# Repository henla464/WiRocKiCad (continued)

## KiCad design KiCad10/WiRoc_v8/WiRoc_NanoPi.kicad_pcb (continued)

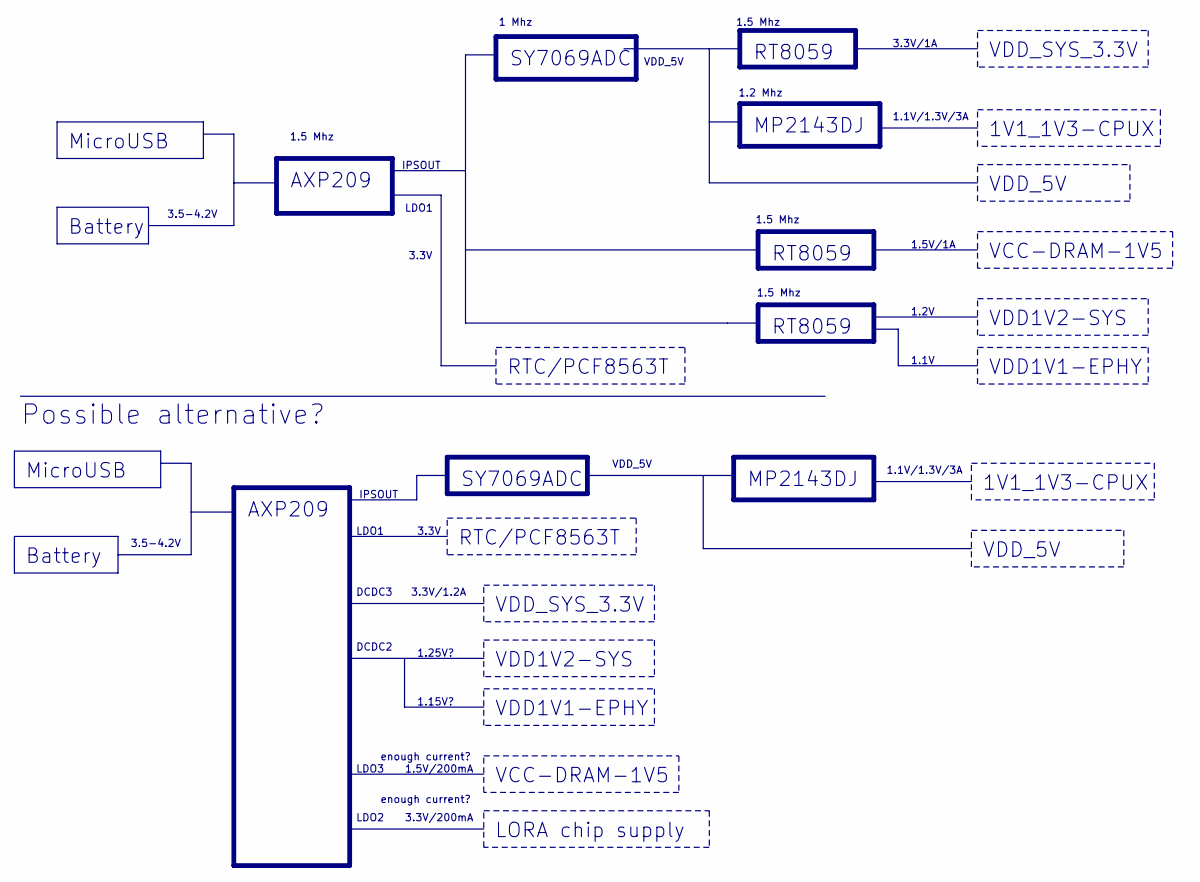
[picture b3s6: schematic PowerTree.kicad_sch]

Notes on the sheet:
1.5 Mhz
1.5V/1A
3.5-4.2V
DCDC3
1.1V/1.3V/3A
Possible alternative?
3.3V/1.2A
1.5V/200mA
1.25V?
IPSOUT
1 Mhz
LDO2
3.3V/1A
3.3V/200mA
1.2V
1.15V?
DCDC2
VDD_5V
LDO1
1.2 Mhz
LDO3
3.3V
1.1V
enough current?
VDD1V1-EPHY
1V1_1V3-CPUX
MicroUSB
RTC/PCF8563T
SY7069ADC
Battery
VDD1V2-SYS
MP2143DJ
RT8059
VDD_SYS_3.3V
AXP209
VCC-DRAM-1V5
LORA chip supply

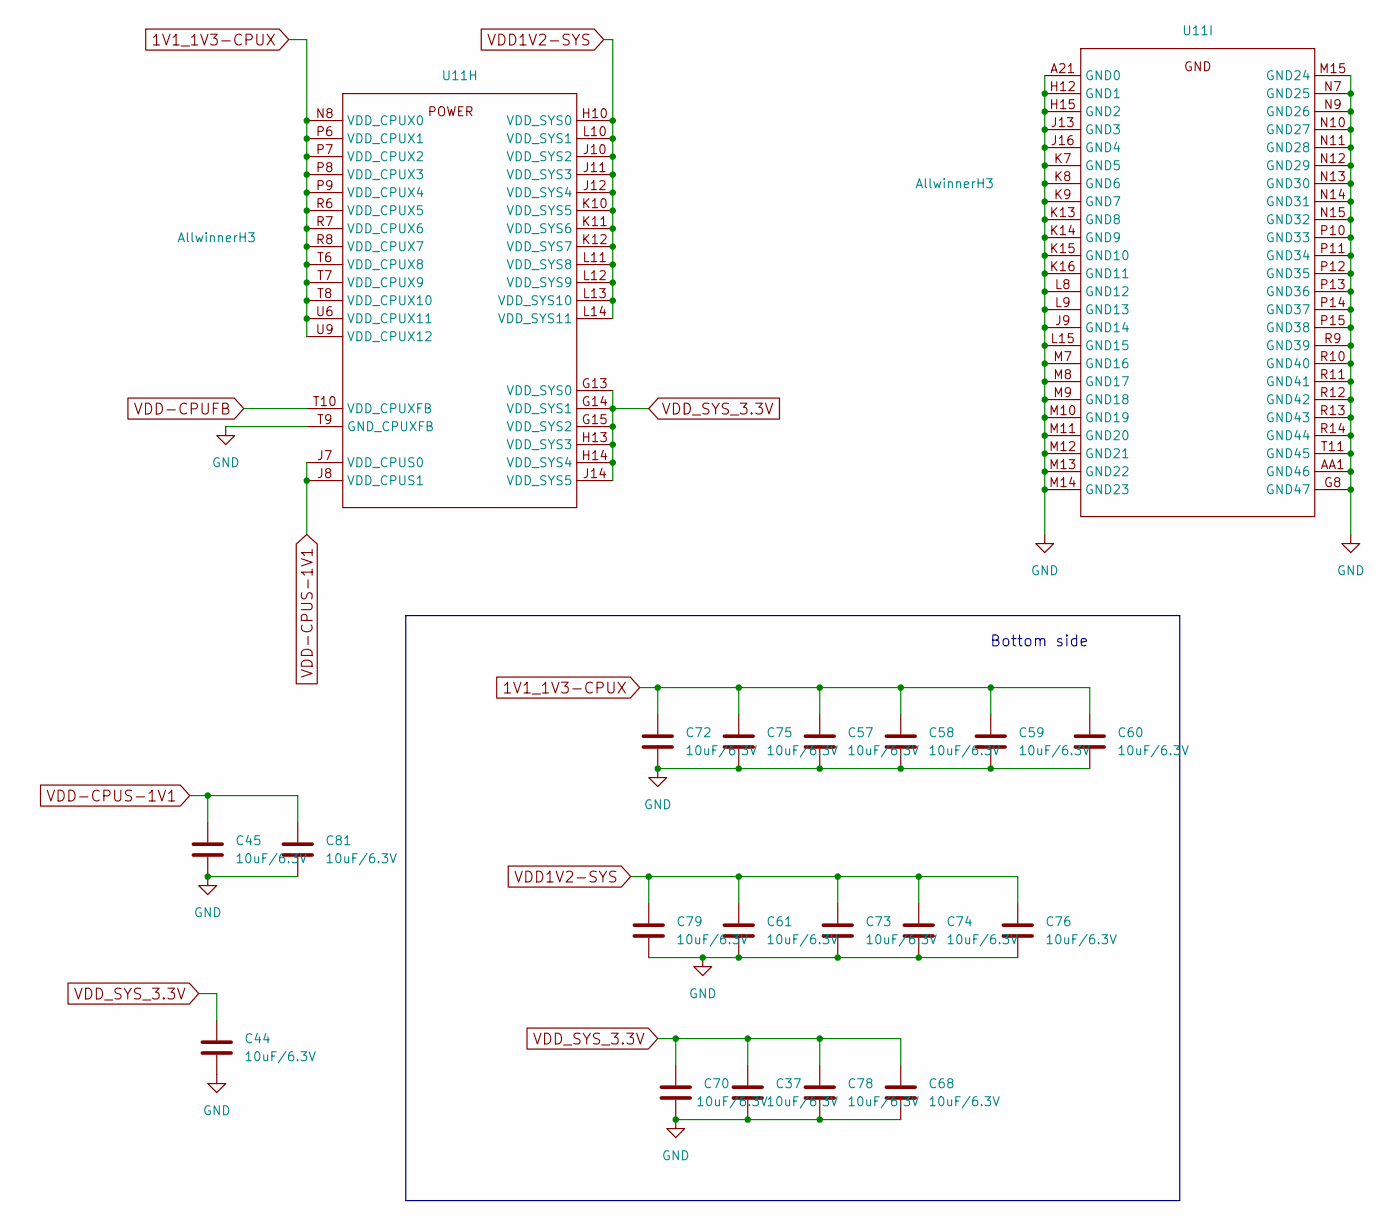
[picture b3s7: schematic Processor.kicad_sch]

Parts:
C37, C44, C45, C57, C58, C59, C60, C61, C68, C70, C72, C73, C74, C75, C76, C78, C79, C81: 10uF/6.3V; C_0402_1005Metric; ManufacturerPartNumber CL05A106MQ5NUNC; LCSC Part # C15525
U11: AllwinnerH3; BGA-347_21x21_14.0x14.0mm; ManufacturerPartNumber H3; JLCBasicExtended Extended

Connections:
1V1_1V3-CPUX: C57.1, C58.1, C59.1, C60.1, C72.1, C75.1, U11.N8 (VDD_CPUX0), U11.P6 (VDD_CPUX1), U11.P7 (VDD_CPUX2), U11.P8 (VDD_CPUX3), U11.P9 (VDD_CPUX4), U11.R6 (VDD_CPUX5), U11.R7 (VDD_CPUX6), U11.R8 (VDD_CPUX7), U11.T6 (VDD_CPUX8), U11.T7 (VDD_CPUX9), U11.T8 (VDD_CPUX10), U11.U6 (VDD_CPUX11), U11.U9 (VDD_CPUX12); also elsewhere on the board
GND: C37.2, C44.2, C45.2, C57.2, C58.2, C59.2, C60.2, C61.2, C68.2, C70.2, C72.2, C73.2, C74.2, C75.2, C76.2, C78.2, C79.2, C81.2, U11.A21 (GND0), U11.AA1 (GND46), U11.G8 (GND47), U11.H12 (GND1), U11.H15 (GND2), U11.J9 (GND14), U11.J13 (GND3), U11.J16 (GND4), U11.K7 (GND5), U11.K8 (GND6), U11.K9 (GND7), U11.K13 (GND8), U11.K14 (GND9), U11.K15 (GND10), U11.K16 (GND11), U11.L8 (GND12), U11.L9 (GND13), U11.L15 (GND15), U11.M7 (GND16), U11.M8 (GND17), U11.M9 (GND18), U11.M10 (GND19), U11.M11 (GND20), U11.M12 (GND21), U11.M13 (GND22), U11.M14 (GND23), U11.M15 (GND24), U11.N7 (GND25), U11.N9 (GND26), U11.N10 (GND27), U11.N11 (GND28), U11.N12 (GND29), U11.N13 (GND30), U11.N14 (GND31), U11.N15 (GND32), U11.P10 (GND33), U11.P11 (GND34), U11.P12 (GND35), U11.P13 (GND36), U11.P14 (GND37), U11.P15 (GND38), U11.R9 (GND39), U11.R10 (GND40), U11.R11 (GND41), U11.R12 (GND42), U11.R13 (GND43), U11.R14 (GND44), U11.T9 (GND_CPUXFB), U11.T11 (GND45); also elsewhere on the board
VDD1V2-SYS: C61.1, C73.1, C74.1, C76.1, C79.1, U11.H10 (VDD_SYS0), U11.J10 (VDD_SYS2), U11.J11 (VDD_SYS3), U11.J12 (VDD_SYS4), U11.K10 (VDD_SYS5), U11.K11 (VDD_SYS6), U11.K12 (VDD_SYS7), U11.L10 (VDD_SYS1), U11.L11 (VDD_SYS8), U11.L12 (VDD_SYS9), U11.L13 (VDD_SYS10), U11.L14 (VDD_SYS11); also elsewhere on the board
VDD-CPUFB: U11.T10 (VDD_CPUXFB); also elsewhere on the board
VDD-CPUS-1V1: C45.1, C81.1, U11.J7 (VDD_CPUS0), U11.J8 (VDD_CPUS1); also elsewhere on the board
VDD_SYS_3.3V: C37.1, C44.1, C68.1, C70.1, C78.1, U11.G13 (VDD_SYS0), U11.G14 (VDD_SYS1), U11.G15 (VDD_SYS2), U11.H13 (VDD_SYS3), U11.H14 (VDD_SYS4), U11.J14 (VDD_SYS5); also elsewhere on the board

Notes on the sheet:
Bottom side

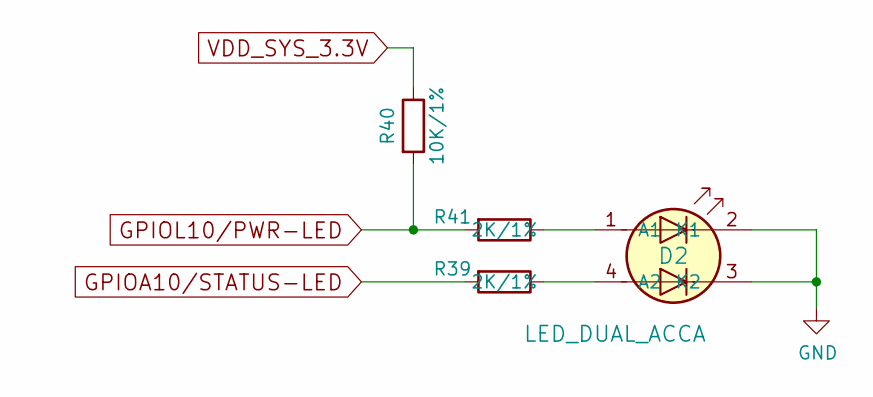
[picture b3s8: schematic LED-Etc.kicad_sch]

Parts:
D2: LED_DUAL_ACCA; LED_Dual_1.7_1.6; ManufacturerPartNumber HL-PCB-1617S9FH203BC; LCSC Part # C513363
R39, R41: 2K/1%; R_0402_1005Metric; ManufacturerPartNumber 0402WGF2001TCE; LCSC Part # C4109
R40: 10K/1%; R_0402_1005Metric; ManufacturerPartNumber 0402WGF1002TCE; LCSC Part # C25744

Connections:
GPIOA10/STATUS-LED: R39.2; also elsewhere on the board
GND: D2.2 (K1), D2.3 (K2); also elsewhere on the board
GPIOL10/PWR-LED: R40.2, R41.2; also elsewhere on the board
unnamed: D2.1 (A1), R41.1
unnamed: D2.4 (A2), R39.1
VDD_SYS_3.3V: R40.1; also elsewhere on the board

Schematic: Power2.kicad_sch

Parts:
C22, C62, C64, C65, C89, C90, C91, C92: 10uF/6.3V; C_0402_1005Metric; ManufacturerPartNumber CL05A106MQ5NUNC; LCSC Part # C15525
L2, L4, L5: DFE252010P-2R2M=P2; L_1008_2520Metric; ManufacturerPartNumber DFE252010P-2R2M=P2; JLCBasicExtended Extended
R42, R46: 10K/1%; R_0402_1005Metric; ManufacturerPartNumber 0402WGF1002TCE; LCSC Part # C25744
R44, R47, R48, R51: 10K/1%; R_0402_1005Metric; ManufacturerPartNumber 0402WGF1002TCE; JLCBasicExtended Basic
R45: 15K/1%; R_0402_1005Metric; ManufacturerPartNumber 0402WGF1502TCE; JLCBasicExtended Basic
R49: 2R/1%; R_0402_1005Metric; ManufacturerPartNumber FRC0402F2R00TS; JLCBasicExtended Extended
R52: 47K/1%; R_0402_1005Metric; ManufacturerPartNumber 0402WGF4702TCE; JLCBasicExtended Basic
U15, U16, U17: RT8059; TSOT-23-5; ManufacturerPartNumber RT8059GJ5; JLCBasicExtended Extended

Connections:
EXTEN: U17.1 (EN); also elsewhere on the board
GND: C22.2, C62.2, C64.2, C65.2, C89.2, C90.2, C91.2, C92.2, R44.2, R47.2, R51.2, U15.2 (GND), U16.2 (GND), U17.2 (GND); also elsewhere on the board
GPIOL8/PWR-STB: R46.2, U16.1 (EN); also elsewhere on the board
GPIOL9/PWR-DRAM: R42.2, U15.1 (EN); also elsewhere on the board
IPSOUT: C64.1, C89.1, U15.4 (IN), U16.4 (IN); also elsewhere on the board
unnamed: R44.1, R45.1, U15.5 (FB)
unnamed: L2.1, U15.3 (LX)
unnamed: R47.1, R48.1, U16.5 (FB)
unnamed: L4.1, U16.3 (LX)
unnamed: R51.1, R52.1, U17.5 (FB)
unnamed: L5.1, U17.3 (LX)
VCC-DRAM-1V5: C62.1, C65.1, L2.2, R45.2; also elsewhere on the board
VDD1V1-EPHY: R49.2; also elsewhere on the board
VDD1V2-SYS: C90.1, L4.2, R48.2, R49.1; also elsewhere on the board
VDD_5V: C91.1, U17.4 (IN); also elsewhere on the board
VDD_SYS_3.3V: C22.1, C92.1, L5.2, R42.1, R46.1, R52.2; also elsewhere on the board

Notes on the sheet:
Vfb=0.6V
Maybe create VDD1V2-SYS with APX209 DCDC2. Voltage only seem to be controlled by register that loses value if it loses power. https://github.com/Squonk42/V3s_Documentation/ AXP203 (209 probably same) seem to indicate it defaults to 1.25V/1.6A when VIN2 set to APS (close enough?) Need to add enable/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
1.5V/1A
Added due to DC bias derating
Maybe create VCC_SYS_3.3V with AXP209 DCDC3 but unsure about if it can provide enough current and how to set correct voltage. https://github.com/Squonk42/V3s_Documentation/ https://github.com/Squonk42/V3s_Documentation/blob/master/V3S_CDR_STD_V1_0_20150514.pdf Seem to indicate setting VIN3 and DC3S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
Would one of the LDOs give enough current to be used for VCC-DRAM-1V5? They seem to be limited to 200mA.
Use LDO for lora chip for less noise? Lora chip need to take 3.3 (or lower) and current < 200 mA?
3.3V/1A
SYSTEM 1.2V

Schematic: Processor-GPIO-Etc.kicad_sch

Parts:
C69: 10uF/6.3V; C_0402_1005Metric; ManufacturerPartNumber CL05A106MQ5NUNC; LCSC Part # C15525
R25: 2K/1%; R_0402_1005Metric; ManufacturerPartNumber 0402WGF2001TCE; JLCBasicExtended Basic
R33, R35: 10K/1%; R_0402_1005Metric; ManufacturerPartNumber 0402WGF1002TCE; LCSC Part # C25744
R34, R43, R62: 33R; R_0402_1005Metric; ManufacturerPartNumber 0402WGF330JTCE; JLCBasicExtended Basic
U11: AllwinnerH3; BGA-347_21x21_14.0x14.0mm; ManufacturerPartNumber H3; JLCBasicExtended Extended

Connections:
GPIOA10/STATUS-LED: U11.E11 (PA10/SIM_DET/PA_EINT10); also elsewhere on the board
/Processor-GPIO-Etc/WIFI-SPI-MOSI-2: R43.1, U11.C15 (PC0/NAND_WE/SPI0_MOSI)
GND: C69.2, R33.2; also elsewhere on the board
IRQ: U11.E13 (PA3/UART2_CTS/JTAG_DI0/PA_EINT3); also elsewhere on the board
LORAAUX: U11.C3 (PG8/UART1_RTS/PG_EINT8); also elsewhere on the board
LORAEN: U11.D6 (PA2/UART2_RTS/JTAG_DO0/PA_EINT2); also elsewhere on the board
unnamed: R62.1, U11.B16 (PC2/NAND_CLE/SPI0_CLK)
unnamed: R33.1, U11.F16 (PC4/NAND_CE0)
unnamed: R34.1, U11.A17 (PC5/NAND_RE/SDC2_CLK)
unnamed: R35.1, U11.A16 (PC7/NAND_RB1)
unnamed: R25.2, U11.H6 (PA5/UART0_RX/PWM0/PA_EINT5)
SCK: U11.F11 (PA11/TWI0_SCK/DI_TX/PA_EINT11); also elsewhere on the board
SDA: U11.C13 (PA12/TWI0_SDA/DI_RX/PA_EINT12); also elsewhere on the board
SDC0-CLK: U11.D20 (PF2/SDC0_CLK/UART0_TX); also elsewhere on the board
SDC0-CMD: U11.F18 (PF3/SDC0_CMD/JTAG_DO0); also elsewhere on the board
SDC0-D0: U11.A19 (PF1/SDC0_D0/JTAG_DI0); also elsewhere on the board
SDC0-D1: U11.D19 (PF0/SDC0_D1/JTAG_MS0); also elsewhere on the board
SDC0-D2: U11.C20 (PF5/SDC0_D2/JTAG_CK0); also elsewhere on the board
SDC0-D3: U11.E21 (PF4/SDC0_D3/UART0_RX); also elsewhere on the board
SDC0-DET: U11.G18 (PF6); also elsewhere on the board
SRR_IRQ: U11.E14 (PA6/SIM_PWREN/PA_EINT6); also elsewhere on the board
SRR_NRST: U11.E3 (PG9/UART1_CTS/PG_EINT9); also elsewhere on the board
UART0_RX: R25.1; also elsewhere on the board
UART0_TX: U11.F5 (PA4/UART0_TX/PA_EINT4); also elsewhere on the board
UART1_RX: U11.D3 (PG7/UART1_RX/PG_EINT7); also elsewhere on the board
UART1_TX: U11.G4 (PG6/UART1_TX/PG_EINT6); also elsewhere on the board
UART2_RX: U11.D5 (PA1/UART2_RX/JTAG_CK0/PA_EINT1); also elsewhere on the board
UART2_TX: U11.D11 (PA0/UART2_TX/JTAG_MS0/PA_EINT0); also elsewhere on the board
VDD_SYS_3.3V: C69.1, R35.2, U11.H7 (VCC_PG), U11.J15 (VCC-PD); also elsewhere on the board
WIFI-DataReady: U11.B13 (PA18/PCM0_SYNC/TWI1_SCK/PA_EINT18); also elsewhere on the board
WIFI-HandShake: U11.D2 (PG11/PCM1_CLK/PG_EINT11); also elsewhere on the board
WIFI-RST: U11.C5 (PE15); also elsewhere on the board
WIFI-SPI-CS0: U11.B15 (PC3/NAND_CE1/SPI0_CS); also elsewhere on the board
WIFI-SPI-MISO: U11.C16 (PC1/NAND_ALE/SPI0_MISO); also elsewhere on the board
WIFI-SPI-MOSI: R43.2; also elsewhere on the board
WIFI-SPI-SCLK: R62.2; also elsewhere on the board
eMMC-CLK: R34.2; also elsewhere on the board
eMMC-CMD: U11.E16 (PC6/NAND_RB0/SDC2_CMD); also elsewhere on the board
eMMC-D0: U11.B18 (PC8/NAND_DQ0/SDC2_D0); also elsewhere on the board
eMMC-D1: U11.C17 (PC9/NAND_DQ1/SDC2_D1); also elsewhere on the board
eMMC-D2: U11.D17 (PC10/NAND_DQ2/SDC2_D2); also elsewhere on the board
eMMC-D3: U11.C18 (PC11/NAND_DQ3/SDC2_D3); also elsewhere on the board
eMMC-D4: U11.B17 (PC12/NAND_DQ4/SDC2_D4); also elsewhere on the board
eMMC-D5: U11.B19 (PC13/NAND_DQ5/SDC2_D5); also elsewhere on the board
eMMC-D6: U11.F17 (PC14/NAND_DQ6/SDC2_D6); also elsewhere on the board
eMMC-D7: U11.C19 (PC15/NAND_DQ7/SDC2_D7); also elsewhere on the board
eMMC-RST: U11.H16 (PC16/NAND_DQS/SDC2_RST); also elsewhere on the board

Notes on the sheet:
Bluetooth/wifi uart
WIFI
(GPIOG8=200, GPIOG9=201, GPIOG11=203)
USB OTG
(GPIOA18=18)
Was DataReady
PC1 was connected to N_VBUSEN but I don't think it was used.
(GPIOE15=143)
GPIOG11 (was on gpio header)
(GPIOE14=142)
LORAUX was previously on GPIOC0 SRR_NRST was previously on GPIOC3
(GPIOC0=64, GPIOC1=65, GPIOC2=66, GPIOC3=67)

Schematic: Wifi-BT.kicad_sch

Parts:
U19: ESP32-C5-Board; ESP32Hosted-C6-Board; not fitted

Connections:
GND: U19.10 (GND); also elsewhere on the board
VDD_SYS_3.3V: U19.11 (VDD33); also elsewhere on the board
WIFI-DataReady: U19.3 (DataReady); also elsewhere on the board
WIFI-HandShake: U19.4 (Handshake); also elsewhere on the board
WIFI-RST: U19.12 (EN); also elsewhere on the board
WIFI-SPI-CS0: U19.9 (CS0); also elsewhere on the board
WIFI-SPI-MISO: U19.7 (MISO); also elsewhere on the board
WIFI-SPI-MOSI: U19.8 (MOSI); also elsewhere on the board
WIFI-SPI-SCLK: U19.6 (SCLK); also elsewhere on the board

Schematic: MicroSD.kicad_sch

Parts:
C30: 10uF/6.3V; C_0402_1005Metric; ManufacturerPartNumber CL05A106MQ5NUNC; LCSC Part # C15525
J3: Micro_SD_Card_Det1; TF-SMD_TF-018B-H15; ManufacturerPartNumber TF-018B-H15; LCSC Part # C2962372
R22: 33R; R_0402_1005Metric; ManufacturerPartNumber 0402WGF330JTCE; JLCBasicExtended Basic
R23, R24: 47K/1%; R_0402_1005Metric; ManufacturerPartNumber 0402WGF4702TCE; JLCBasicExtended Basic

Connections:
/MicroSD/SDC0-CLK-2: J3.5 (CLK), R22.2
GND: C30.1, J3.6 (VSS), J3.10 (SHIELD), R24.1; also elsewhere on the board
SDC0-CLK: R22.1; also elsewhere on the board
SDC0-CMD: J3.3 (CMD), R23.1; also elsewhere on the board
SDC0-D0: J3.7 (DAT0); also elsewhere on the board
SDC0-D1: J3.8 (DAT1); also elsewhere on the board
SDC0-D2: J3.1 (DAT2); also elsewhere on the board
SDC0-D3: J3.2 (DAT3/CD); also elsewhere on the board
SDC0-DET: R24.2; also elsewhere on the board
VDD_SYS_3.3V: C30.2, J3.4 (VDD), R23.2; also elsewhere on the board

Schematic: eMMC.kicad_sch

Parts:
C32, C33, C66, C67, C71, C83, C84, C85: 10uF/6.3V; C_0402_1005Metric; ManufacturerPartNumber CL05A106MQ5NUNC; LCSC Part # C15525
R26: 10K/1%; R_0402_1005Metric; ManufacturerPartNumber 0402WGF1002TCE; LCSC Part # C25744
U14: KLM8G1GETF-B041; MICRON_EMMC_153; ManufacturerPartNumber KLM8G1GETF-B041; JLCBasicExtended Extended

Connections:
GND: C32.2, C33.2, C66.2, C67.2, C71.2, C83.2, C84.2, C85.2, U14.A6 (Vss), U14.C4 (Vss), U14.D4 (NC33), U14.E7 (Vss), U14.G5 (Vss), U14.H10 (Vss), U14.J5 (Vss), U14.K8 (Vss), U14.N2 (Vss), U14.N5 (Vss), U14.P2 (NC102), U14.P4 (Vss), U14.P6 (Vss), U14.P8 (NC103); also elsewhere on the board
unnamed: C32.1, C33.1, U14.C1 (NC19), U14.C2 (VDDI)
VDD_SYS_3.3V: C66.1, C67.1, C71.1, C83.1, C84.1, C85.1, R26.1, U14.C6 (VDD), U14.E6 (VDDF), U14.F5 (VDDF), U14.J10 (VDDF), U14.K9 (VDDF), U14.M4 (VDD), U14.N4 (VDD), U14.P3 (VDD), U14.P5 (VDD); also elsewhere on the board
eMMC-CLK: U14.M6 (CLK); also elsewhere on the board
eMMC-CMD: R26.2, U14.M5 (CMD); also elsewhere on the board
eMMC-D0: U14.A3 (DAT0); also elsewhere on the board
eMMC-D1: U14.A4 (DAT1); also elsewhere on the board
eMMC-D2: U14.A5 (DAT2); also elsewhere on the board
eMMC-D3: U14.B1 (NC10), U14.B2 (DAT3); also elsewhere on the board
eMMC-D4: U14.A2 (NC2), U14.B3 (DAT4); also elsewhere on the board
eMMC-D5: U14.B4 (DAT5), U14.C3 (NC20), U14.D1 (NC30), U14.D2 (NC31); also elsewhere on the board
eMMC-D6: U14.B5 (DAT6), U14.C5 (NC21); also elsewhere on the board
eMMC-D7: U14.B6 (DAT7); also elsewhere on the board
eMMC-RST: U14.K5 (RSTN); also elsewhere on the board

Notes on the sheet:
* Connected to simplify fanout from the eMMC chip

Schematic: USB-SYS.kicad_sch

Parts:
C31, C38, C39, C77, C82: 10uF/6.3V; C_0402_1005Metric; ManufacturerPartNumber CL05A106MQ5NUNC; LCSC Part # C15525
C36: 1uF; C_0402_1005Metric; ManufacturerPartNumber CL05A105KA5NQNC; LCSC Part # C52923
C40, C41: 22pF; C_0402_1005Metric; ManufacturerPartNumber 0402CG220J500NT; JLCBasicExtended Basic
C42, C43: 100nF; C_0402_1005Metric; ManufacturerPartNumber CL05B104KO5NNNC; LCSC Part # C1525
R27: 47K/1%; R_0402_1005Metric; ManufacturerPartNumber 0402WGF4702TCE; JLCBasicExtended Basic
R28: 100K-1%; R_0402_1005Metric; ManufacturerPartNumber 0402WGF1003TCE; JLCBasicExtended Basic
R29, R30, R31, R32: 10K/1%; R_0402_1005Metric; ManufacturerPartNumber 0402WGF1002TCE; LCSC Part # C25744
R60, R61: 12K/1%; R_0402_1005Metric; ManufacturerPartNumber 0402WGF1202TCE; JLCBasicExtended Basic
U11: AllwinnerH3; BGA-347_21x21_14.0x14.0mm; ManufacturerPartNumber H3; JLCBasicExtended Extended
U13: SGM803-RXN3L; SOT-23-3; ManufacturerPartNumber SGM803-RXN3L/TR; JLCBasicExtended Extended
Y2: 24MHz/CL=12pF; Crystal_SMD_2520-4Pin_2.5x2.0mm; ManufacturerPartNumber TXM24M0004252FBCEO00T; JLCBasicExtended Extended

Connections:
AP-RESET: C42.1, R29.2, U11.V6 (RESET), U13.2 (/RESET)
EPHY_RXN: U11.A4 (EPHY_RXN); also elsewhere on the board
EPHY_RXP: U11.B4 (EPHY_RXP); also elsewhere on the board
EPHY_TXN: U11.A3 (EPHY_TXN); also elsewhere on the board
EPHY_TXP: U11.B3 (EPHY_TXP); also elsewhere on the board
GND: C31.2, C36.1, C38.2, C39.1, C40.1, C41.1, C42.2, C43.2, C77.2, C82.2, R60.2, R61.2, U11.H8 (GND_TV), U11.M5 (HGND), U11.U3 (AGND), U13.1 (GND), Y2.2 (G), Y2.4 (G); also elsewhere on the board
GPIOL6/CPUX-VSET: U11.T4 (PL6/S_JTAG_DO/S_PL_EINT6); also elsewhere on the board
GPIOL8/PWR-STB: U11.T2 (PL8/S_PL_EINT8); also elsewhere on the board
GPIOL9/PWR-DRAM: U11.M6 (PL9/S_PL_EINT9); also elsewhere on the board
GPIOL10/PWR-LED: U11.V2 (PL10/S_PWM/S_PL_EINT10); also elsewhere on the board
LORAIRQ: U11.U2 (PL11/S_CIR_RX/S_PL_EINT11); also elsewhere on the board
unnamed: R30.1, U11.R1 (PL3/S_UART_RX/S_PL_EINT3)
unnamed: R31.1, U11.N2 (PL4/S_JTAG_MS/S_PL_EINT4)
unnamed: R60.1, R61.1, U11.F6 (EPHY_RTX)
unnamed: C36.2, U11.W3 (MBIAS)
unnamed: R28.2, U11.AA5 (KEYADC)
unnamed: R27.2, U11.AA6 (NMI)
unnamed: R32.1, U11.W6 (UBOOT)
unnamed: C38.1, U11.H11 (VDD_EFUSEBP)
USBHost1-DN: U11.A8 (USB_DM2); also elsewhere on the board
USBHost1-DP: U11.A7 (USB_DP2); also elsewhere on the board
USBHost2-DN: U11.B9 (USB_DM3); also elsewhere on the board
USBHost2-DP: U11.B8 (USB_DP3); also elsewhere on the board
VDD1V1-EPHY: U11.F8 (EPHY_VDD); also elsewhere on the board
VDD-CPUS-1V1: C82.1, U11.M4 (RTC_VIO); also elsewhere on the board
VDD_SYS_3.3V: C31.1, C39.2, C43.1, C77.1, R27.1, R28.1, R29.1, R30.2, R31.2, R32.2, U11.G7 (EPHY_VCC), U11.G9 (V33_TV), U11.G10 (VDD_EFUSE), U11.G11 (VCC-USB), U11.J6 (HVCC), U11.K6 (VCC_RTC), U11.N3 (VCC_PLL), U11.V3 (AVCC), U13.3 (Vin); also elsewhere on the board
X24MI: C40.2, U11.K2 (X24MIN), Y2.1
X24MO: C41.2, U11.K1 (X24MOUT), Y2.3

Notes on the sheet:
Close to IC
RTC_VIO is connected to an internal LDO output (powered from VCC_RTC?) Default voltage 1.1v, controlled by register
wifi clock,shouldn't be needed
WIFI (enable)

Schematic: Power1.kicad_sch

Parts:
C93, C95, C96: 10uF/6.3V; C_0402_1005Metric; ManufacturerPartNumber CL05A106MQ5NUNC; LCSC Part # C15525
C94: 22pF; C_0402_1005Metric; ManufacturerPartNumber 0402CG220J500NT; LCSC Part # C1555
L6: DFE252010P-1R0M=P2; L_1008_2520Metric; ManufacturerPartNumber DFE252010P-1R0M=P2; JLCBasicExtended Extended
Q1: L2N7002WT1G; SOT-323_SC-70; ManufacturerPartNumber L2N7002WT1G; JLCBasicExtended Extended
R50: 10K/1%; R_0402_1005Metric; ManufacturerPartNumber 0402WGF1002TCE; JLCBasicExtended Basic
R53: 12K/1%; R_0402_1005Metric; ManufacturerPartNumber 0402WGF1202TCE; JLCBasicExtended Basic
R54: 33K/1%; R_0402_1005Metric; ManufacturerPartNumber 0402WGF3302TCE; JLCBasicExtended Basic
R55: 10K/1%; R_0402_1005Metric; ManufacturerPartNumber 0402WGF1002TCE; LCSC Part # C25744
U18: MP2143DJ; TSOT-23-8-Thinner-Pads; ManufacturerPartNumber MP2143DJ-LF-Z; JLCBasicExtended Extended

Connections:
1V1_1V3-CPUX: C95.1, C96.1, L6.2, U18.5 (OUT); also elsewhere on the board
GND: C93.2, C95.2, C96.2, Q1.2 (S), R53.1, U18.4 (GND), U18.6 (GND1); also elsewhere on the board
GPIOL6/CPUX-VSET: Q1.1 (G), R55.1; also elsewhere on the board
GPIOL8/PWR-STB: U18.8 (EN); also elsewhere on the board
unnamed: Q1.3 (D), R54.1
unnamed: C94.2, R50.1, R53.2, R54.2, U18.7 (FB)
unnamed: L6.1, U18.3 (SW)
VDD-CPUFB: C94.1, R50.2; also elsewhere on the board
VDD_5V: C93.1, U18.2 (VIN); also elsewhere on the board
VDD_SYS_3.3V: R55.2; also elsewhere on the board

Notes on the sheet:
GPIOL6/CPUX-VSET = 0, 1V1_1V3-CPUX=1.1V GPIOL6/CPUX-VSET = 1, 1V1_1V3-CPUX=1.3V
1.1V/1.3V/3A
Vfb=0.6V

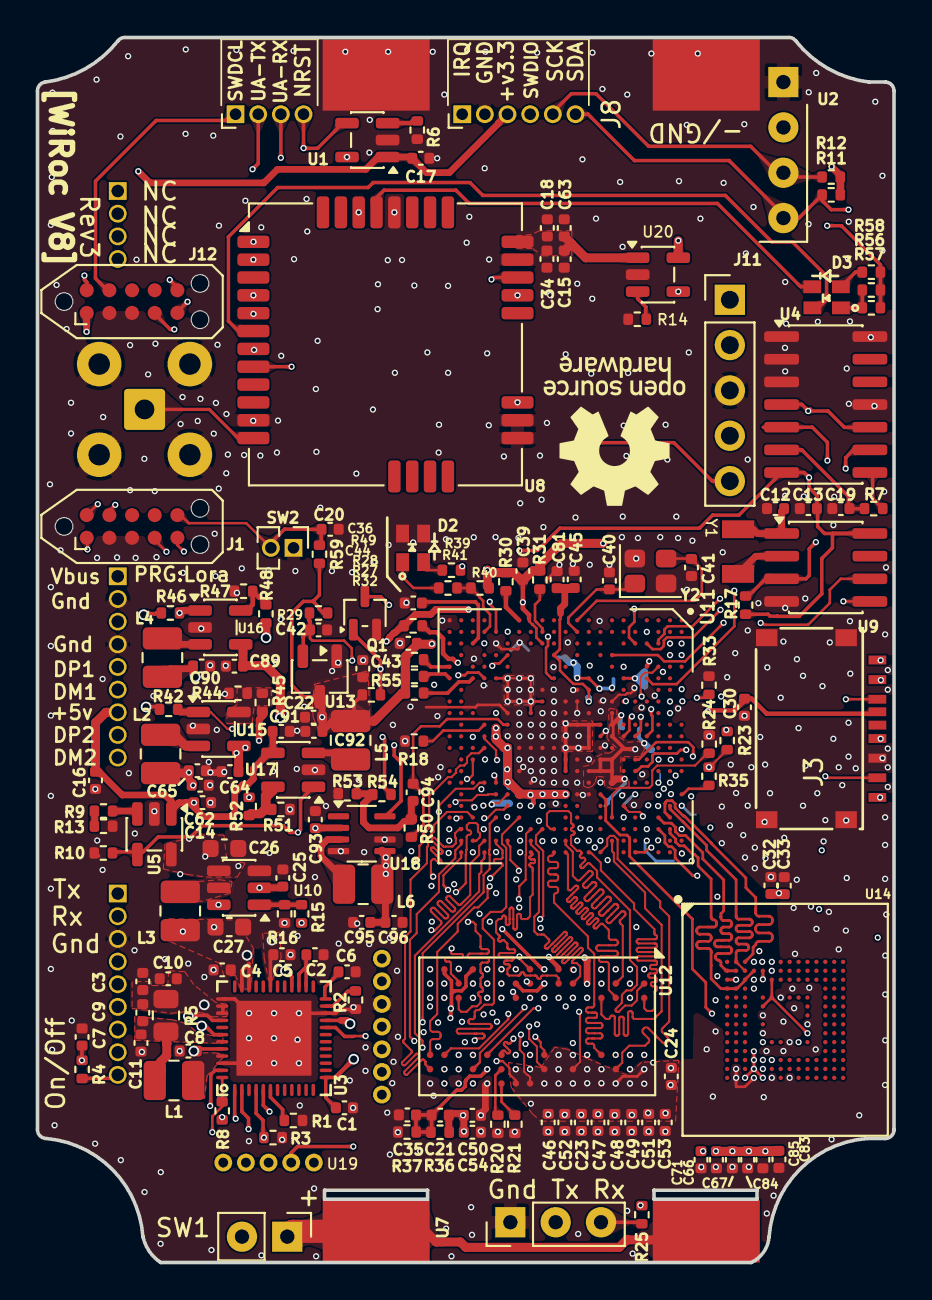
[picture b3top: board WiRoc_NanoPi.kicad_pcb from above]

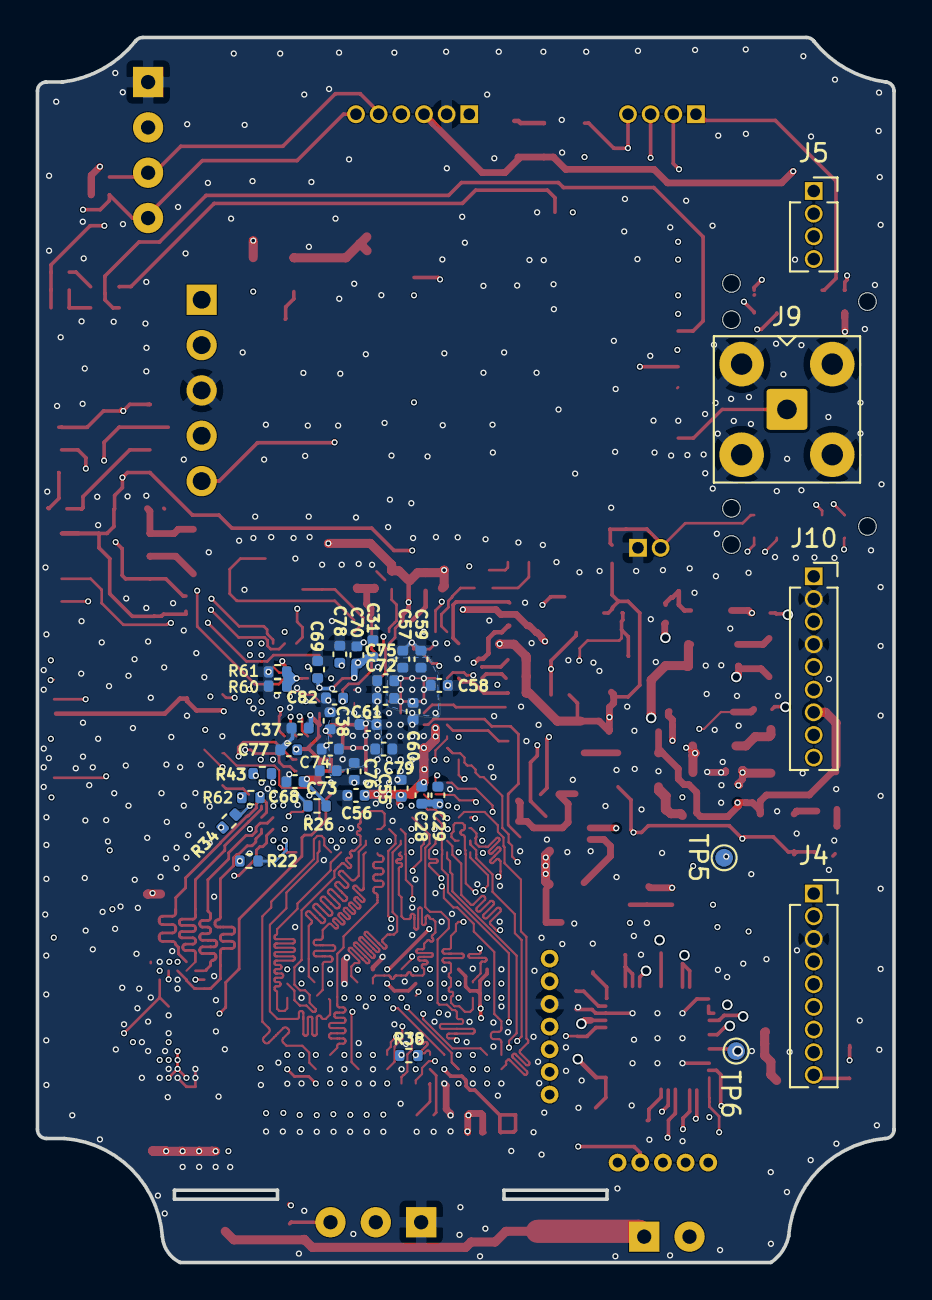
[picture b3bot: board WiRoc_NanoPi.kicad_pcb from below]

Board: 6 copper layers, 48.0 x 68.7 mm, 199 parts (38 on the bottom side), 192 nets.

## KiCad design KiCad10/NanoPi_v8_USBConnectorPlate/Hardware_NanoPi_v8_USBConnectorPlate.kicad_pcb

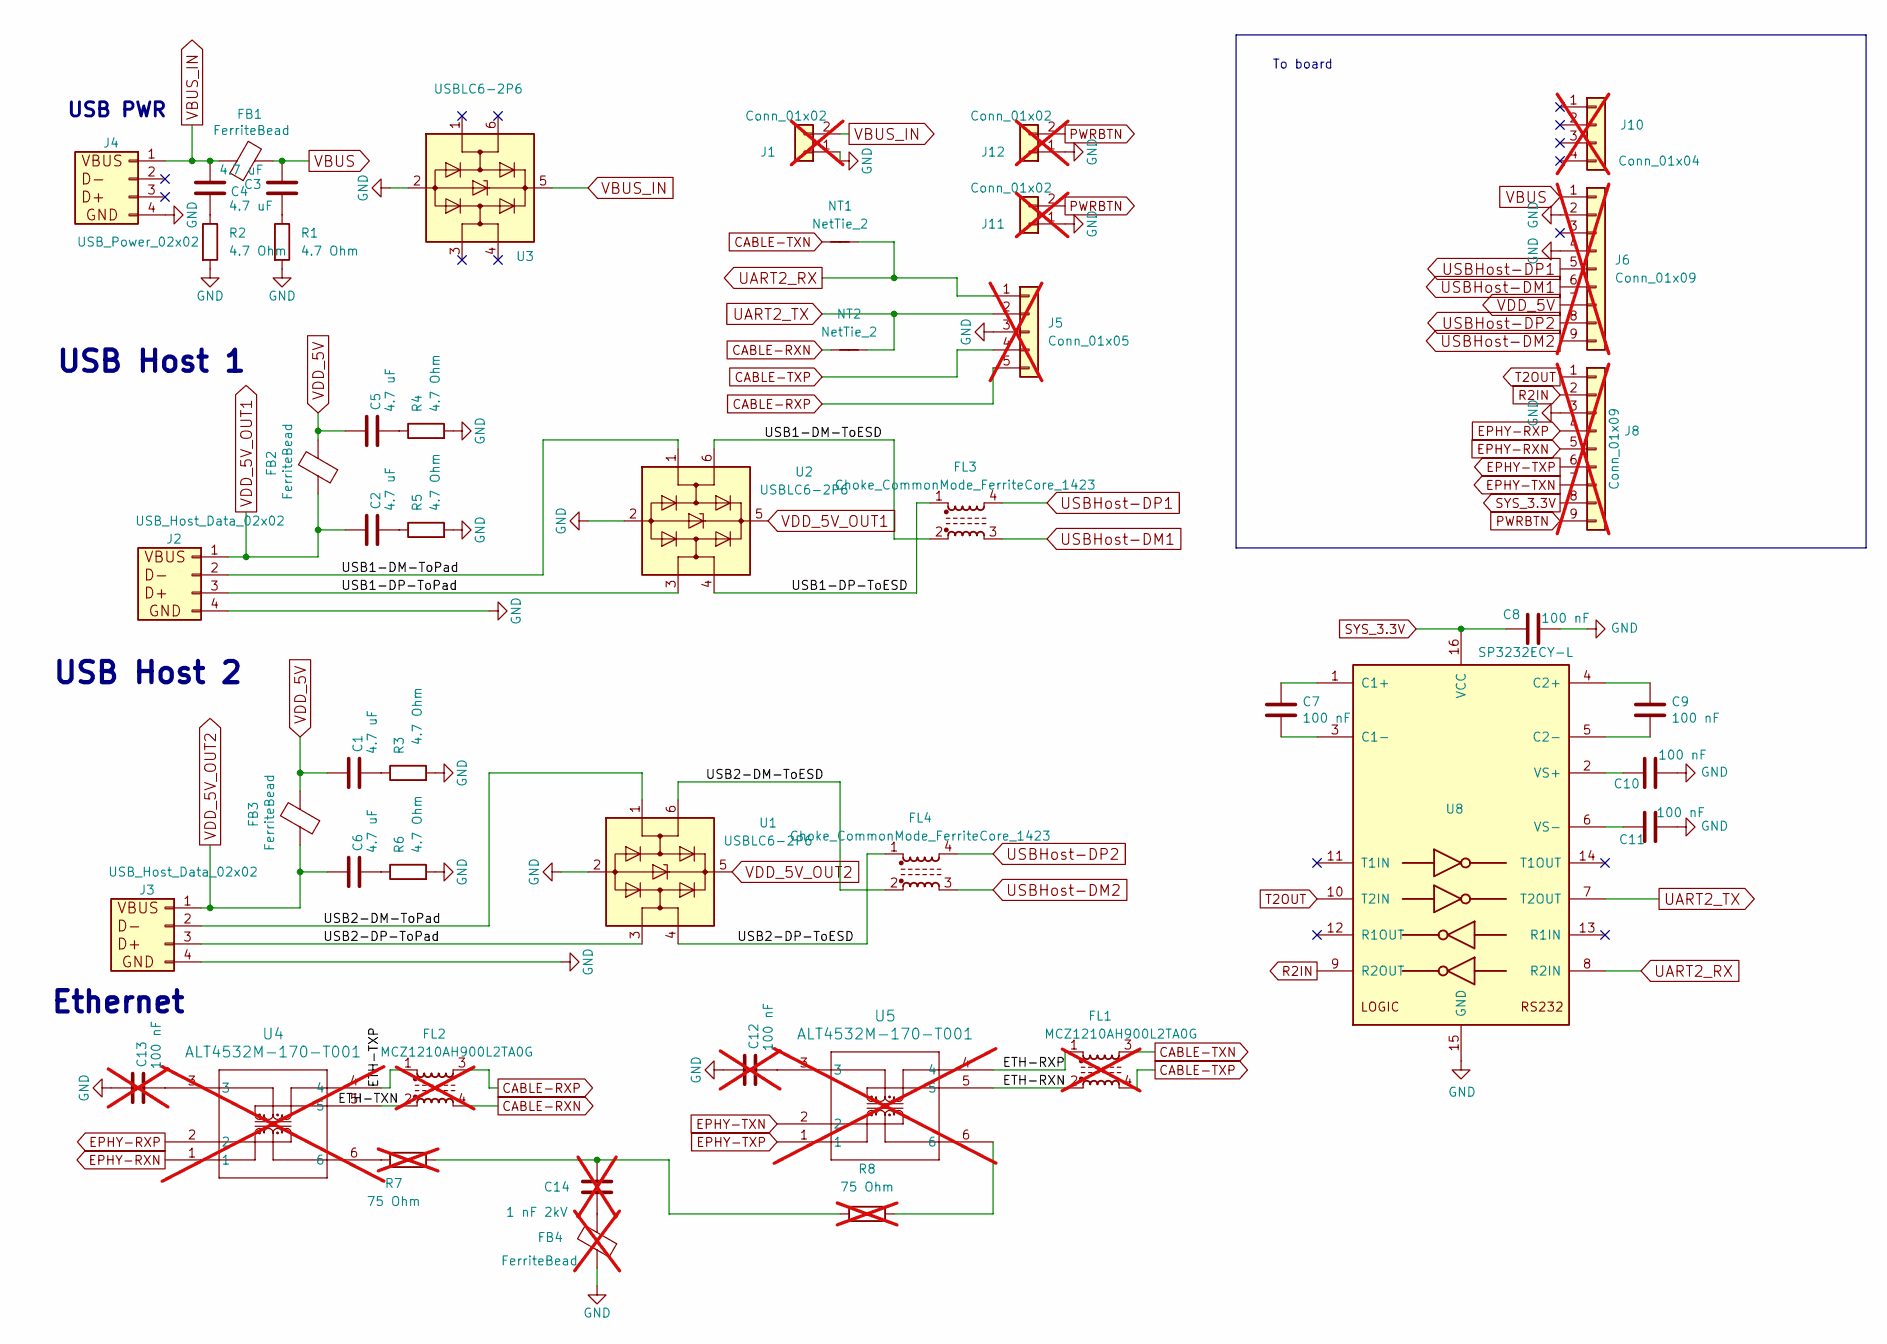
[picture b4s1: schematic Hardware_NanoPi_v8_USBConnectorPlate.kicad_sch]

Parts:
C1, C2, C3, C4, C5, C6: 4.7 uF; C_0402_1005Metric; PartNumber CL05A475MP5NRNC; LCSC C23733
C7: 100 nF; C_0402_1005Metric; ManufacturerPartNumber CC0603KRX7R9BB104; LCSC Part # C1525
C8, C9, C10, C11: 100 nF; C_0402_1005Metric; ManufacturerPartNumber CC0603KRX7R9BB104; LCSC Part # C307331
C12, C13: 100 nF; C_0402_1005Metric; PartNumber CL05A475MP5NRNC; LCSC C307331; not fitted
C14: 1 nF 2kV; C_1206_3216Metric; PartNumber CL05A475MP5NRNC; LCSC C9196; not fitted
FB1, FB2: FerriteBead; L_1206_3216Metric; LCSC C16902
FB3: FerriteBead; L_1206_3216Metric; PartNumber BLM31PG601SN1; LCSC C16902
FB4: FerriteBead; L_1206_3216Metric; PartNumber BLM31PG601SN1; LCSC C16902; not fitted
FL1, FL2: MCZ1210AH900L2TA0G; MCZ1210AH_L2_TDK; LCSC C114784; not fitted
FL3, FL4: Choke_CommonMode_FerriteCore_1423; 0805_CommonModeChoke_1423; LCSC C49023314
J1, J11: Conn_01x02; PinHeader_1x02_P2.54mm_Horizontal; not fitted
J2: USB_Host_Data_02x02; USBConnPads7
J3: USB_Host_Data_02x02; USBConnPads8
J4: USB_Power_02x02; USBConnPads7
J5: Conn_01x05; SerialAndEthConnPads4Pin; not fitted
J6, J8: Conn_01x09; PinHeader_1x09_P1.27mm_Horizontal; not fitted
J10: Conn_01x04; PinHeader_1x04_P1.27mm_Horizontal; not fitted
J12: Conn_01x02; PwrBtnPads; not fitted
NT1, NT2: NetTie_2; NetTie-2_SMD_Pad0.3mm
R1, R2, R3, R4, R5, R6: 4.7 Ohm; R_0603_1608Metric; PartNumber 0603WAF470KT5E; LCSC C23164
R7, R8: 75 Ohm; R_0603_1608Metric; LCSC C4275; not fitted
U1, U2, U3: USBLC6-2P6; SOT-666; LCSC C15999
U4, U5: ALT4532M-170-T001; ALT4532M_TDK; LCSC C2845101; not fitted
U8: SP3232ECY-L; TSSOP-16_4.4x5mm_P0.65mm_PartOfSilkscreenRemoved; ManufacturerPartNumber SP3232ECY-L; LCSC Part # C3028967

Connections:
/ETH-RXN: FL1.2, U5.5
/ETH-RXP: FL1.1, U5.4
/ETH-TXN: FL2.2, U4.5
/ETH-TXP: FL2.1, U4.4
/USB1-DM-ToESD: FL3.2, U2.6 (I/O1)
/USB1-DM-ToPad: J2.2, U2.1 (I/O1)
/USB1-DP-ToESD: FL3.1, U2.4 (I/O2)
/USB1-DP-ToPad: J2.3, U2.3 (I/O2)
/USB2-DM-ToESD: FL4.2, U1.6 (I/O1)
/USB2-DM-ToPad: J3.2, U1.1 (I/O1)
/USB2-DP-ToESD: FL4.1, U1.4 (I/O2)
/USB2-DP-ToPad: J3.3, U1.3 (I/O2)
CABLE-RXN: FL2.4, NT2.1
CABLE-RXP: FL2.3, J5.5
CABLE-TXN: FL1.3, NT1.1
CABLE-TXP: FL1.4, J5.4
EPHY-RXN: J8.5, U4.1
EPHY-RXP: J8.4, U4.2
EPHY-TXN: J8.7, U5.2
EPHY-TXP: J8.6, U5.1
GND: C8.1, C10.1, C11.1, C12.1, C13.1, FB4.1, J1.1, J2.4, J3.4, J4.4, J5.3, J6.2, J6.4, J8.3, J11.1, J12.1, R1.2, R2.2, R3.2, R4.2, R5.2, R6.2, U1.2 (GND), U2.2 (GND), U3.2 (GND), U8.15 (GND)
unnamed: C1.2, R3.1
unnamed: C2.2, R5.1
unnamed: C3.1, R1.1
unnamed: C4.2, R2.1
unnamed: C5.2, R4.1
unnamed: C6.2, R6.1
unnamed: C12.2, U5.3
unnamed: C13.2, U4.3
unnamed: C14.1, R7.2, R8.2
unnamed: C14.2, FB4.2
unnamed: R7.1, U4.6
unnamed: R8.1, U5.6
unnamed: C7.1, U8.1 (C1+)
unnamed: C7.2, U8.3 (C1-)
unnamed: C9.1, U8.4 (C2+)
unnamed: C9.2, U8.5 (C2-)
unnamed: C10.2, U8.2 (VS+)
unnamed: C11.2, U8.6 (VS-)
PWRBTN: J8.9, J11.2, J12.2
R2IN: J8.2, U8.9 (R2OUT)
SYS_3.3V: C8.2, J8.8, U8.16 (VCC)
T2OUT: J8.1, U8.10 (T2IN)
UART2_RX: J5.1, NT1.2, U8.8 (R2IN)
UART2_TX: J5.2, NT2.2, U8.7 (T2OUT)
USBHost-DM1: FL3.3, J6.6
USBHost-DM2: FL4.3, J6.9
USBHost-DP1: FL3.4, J6.5
USBHost-DP2: FL4.4, J6.8
VBUS: C3.2, FB1.2, J6.1
VBUS_IN: C4.1, FB1.1, J1.2, J4.1, U3.5 (VBUS)
VDD_5V: C1.1, C5.1, FB2.2, FB3.2, J6.7
VDD_5V_OUT1: C2.1, FB2.1, J2.1, U2.5 (VBUS)
VDD_5V_OUT2: C6.1, FB3.1, J3.1, U1.5 (VBUS)

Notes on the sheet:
USB PWR
USB Host 1
Ethernet
To board
USB Host 2

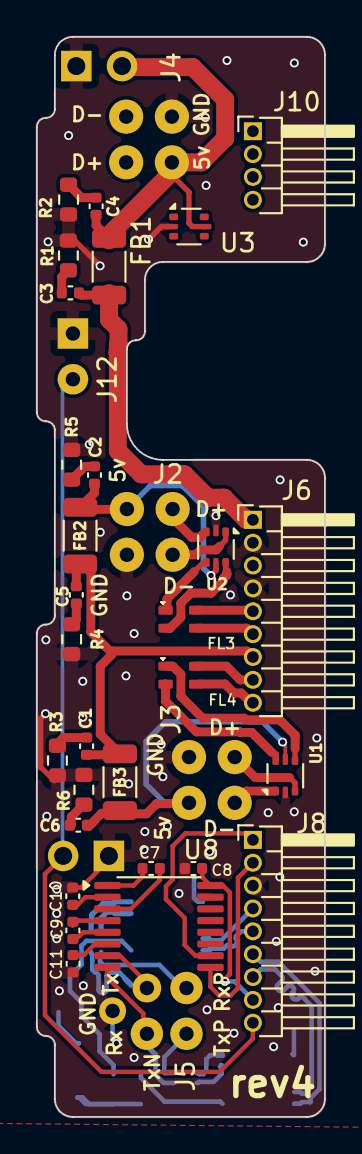
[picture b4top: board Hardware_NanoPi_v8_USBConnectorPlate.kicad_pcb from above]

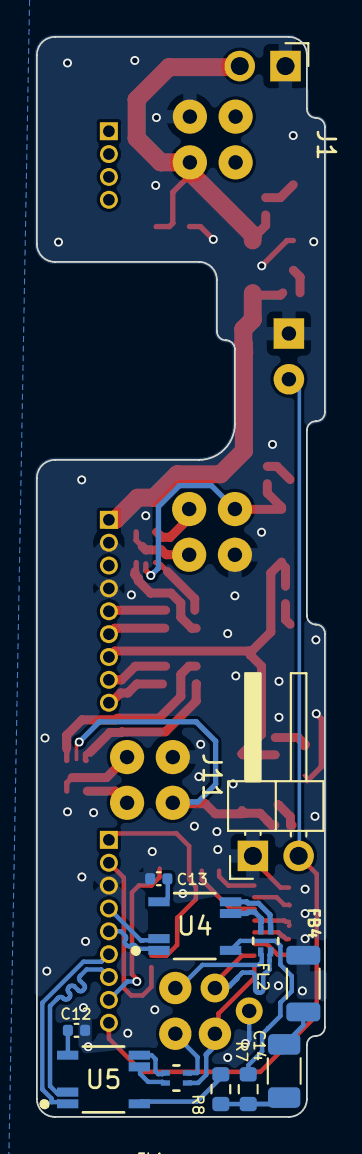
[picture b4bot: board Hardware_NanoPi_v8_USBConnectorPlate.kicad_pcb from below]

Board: 2 copper layers, 16.0 x 60.0 mm, 48 parts (14 on the bottom side), 54 nets.
